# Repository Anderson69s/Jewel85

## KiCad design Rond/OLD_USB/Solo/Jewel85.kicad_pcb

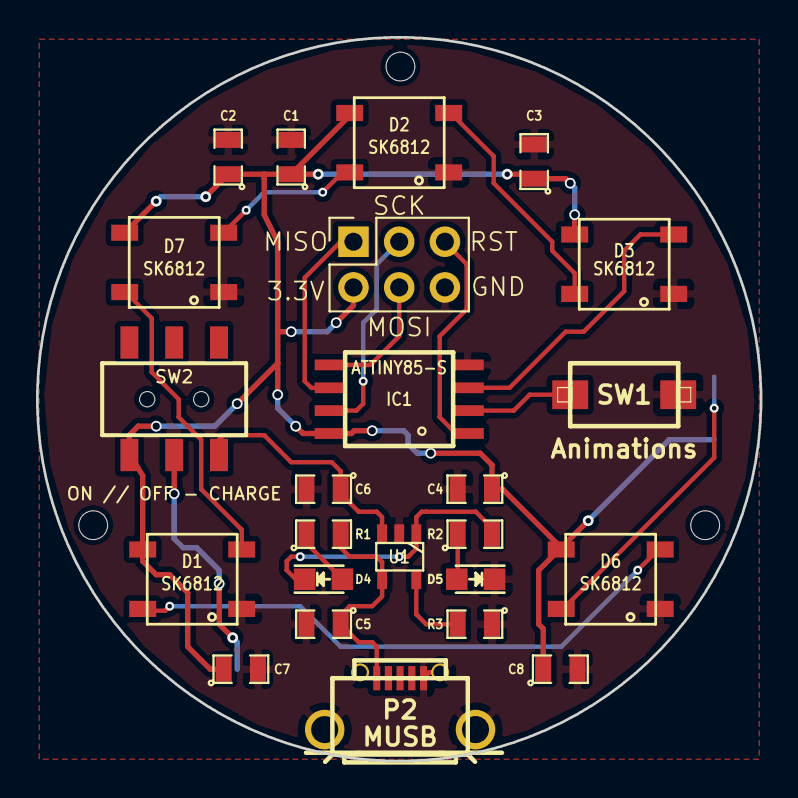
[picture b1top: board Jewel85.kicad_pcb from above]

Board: 2 copper layers, 40.2 x 40.2 mm, 32 parts (0 on the bottom side), 20 nets.

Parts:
C1, C2, C3, C4, C7, C8: 100nF; SM0805
C5, C6: 10μF; SM0805
D1, D2, D3, D6, D7: SK6812; WS2812B
D4: LED ROUGE; LED_0805
D5: LED VERTE; LED_0805
H1, H2, H3: HOLE_1.6MM; Hole_1.6mm
IC1: ATTINY85-S; SOIC8-W
J1: PROG; Socket_Strip_Straight_2x03_Pitch2.54mm
P1: BAT -; PADS_CONNEXION
P2: MUSB; USB_micro_AB_Picots
P3: 3,3V; PADS_CONNEXION
P4: DIN; PADS_CONNEXION
P5: GND; PADS_CONNEXION
P6: BAT +; PADS_CONNEXION
R1, R2: 470; SM0805
R3: 5K; SM0805
SW1: Animations; SWITCH_CMS
SW2: ON // OFF - CHARGE; Switch_DPDT_Large
U1: MCP73831; SOT23-5

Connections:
+3V3: C1.1, C2.1, C3.1, C4.1, C7.1, C8.1, D1.1, D2.1, D3.1, D6.1, D7.1, IC1.8, J1.2, P3.1, SW2.4
GND: C1.2, C2.2, C3.2, C4.2, C5.2, C6.2, C7.2, C8.2, D1.3, D2.3, D3.3, D5.1, D6.3, D7.3, IC1.4, J1.6, P1.1, P2.5, P5.1, R3.1, SW1.2, U1.2
unnamed: C5.1, P2.1, R1.2, U1.4
unnamed: C6.1, SW2.6, U1.3
unnamed: D1.2, D6.4
unnamed: D1.4, D7.2
unnamed: D2.2, D7.4
unnamed: D2.4, D3.2
unnamed: D4.1, R2.2, U1.1
unnamed: D4.2, R1.1
unnamed: D5.2, R2.1
unnamed: D6.2, P4.1
unnamed: P6.1, SW2.5
unnamed: R3.2, U1.5
PB0: IC1.5, J1.4
PB1: IC1.6, J1.1
PB2: IC1.7, J1.3
PB3: IC1.2, SW1.1
PB4: D3.4, IC1.3
RST: IC1.1, J1.5

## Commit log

2018-05-24 1st
    initial commit
2018-05-24 2nd
    add old pcb
2018-05-24 3rd
    removed old repo
2018-06-26 Square Board
    initial design for square board
2018-07-04 Clean and short
    Cleaning and shorting the repo
2018-07-04 3DShapes
    Remove useless 3DShapes
2018-08-06 Case
    Add case
2018-08-06 Finish case
    Case = Done
2018-09-23 Pmma front
    make file for front pmma
2018-09-24 Validation of the front pmma face
    Done
2018-11-04 Clean up
    Sort some files
2019-01-27 Clean UP
    Clean UP
2019-01-30 Forgot Adafruit...
    🙈🙊
